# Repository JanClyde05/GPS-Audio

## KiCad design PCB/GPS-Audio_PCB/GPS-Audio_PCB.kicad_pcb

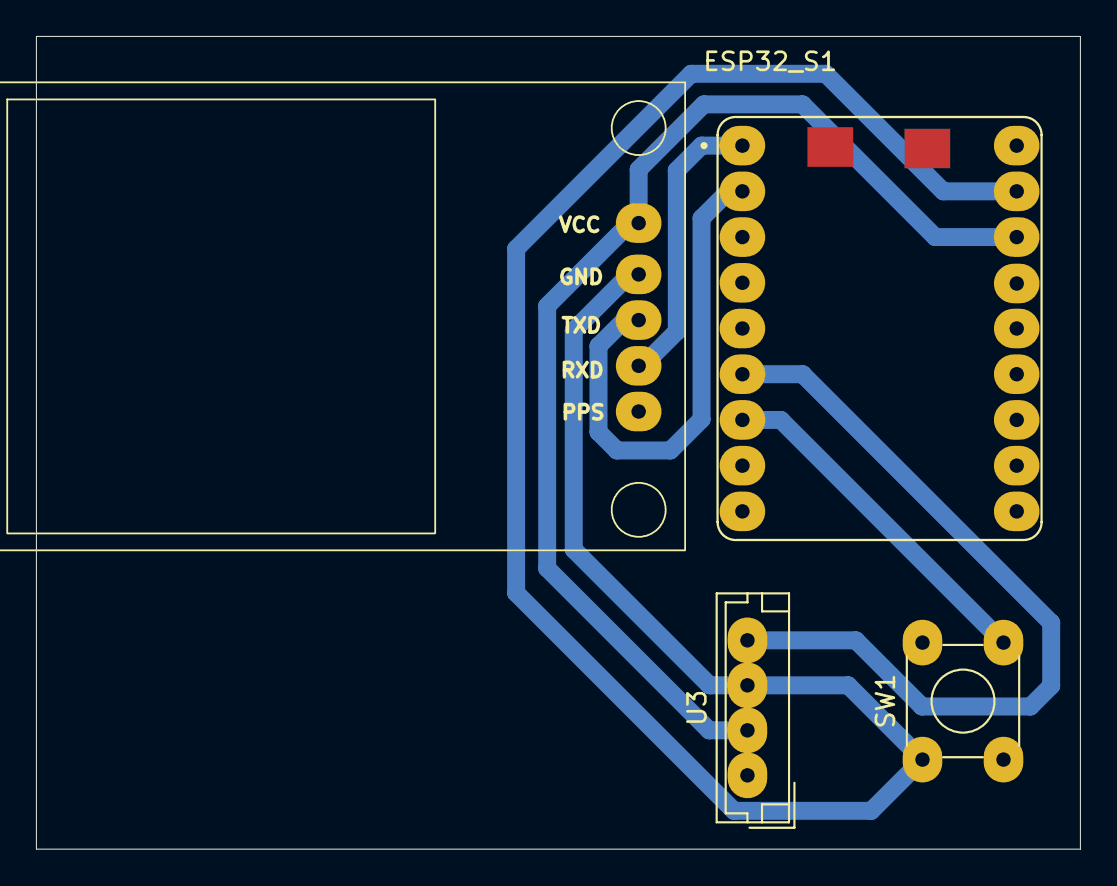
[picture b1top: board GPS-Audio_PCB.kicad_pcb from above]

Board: 2 copper layers, 58.0 x 45.2 mm, 4 parts (0 on the bottom side), 6 nets.

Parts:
ESP32_S1: ESP32-S3-SuperMini
SW1: SW_Push; SW_TH_Tactile_Omron_B3F-100x
U2: NEO7
U3: JST_EH_B4B-EH-A_1x04_P2.50mm_Vertical

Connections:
+3V3: ESP32_S1.3V3, U2.1 (VCC), U3.2 (VCC)
GND: ESP32_S1.GND, SW1.1, U2.2 (GND), U3.3 (GND)
GPS RX: ESP32_S1.TX, U2.4 (RX)
GPS TX: ESP32_S1.RX, U2.3 (TX)
MIC: ESP32_S1.4, U3.4 (A0)
unnamed: ESP32_S1.5, SW1.2
